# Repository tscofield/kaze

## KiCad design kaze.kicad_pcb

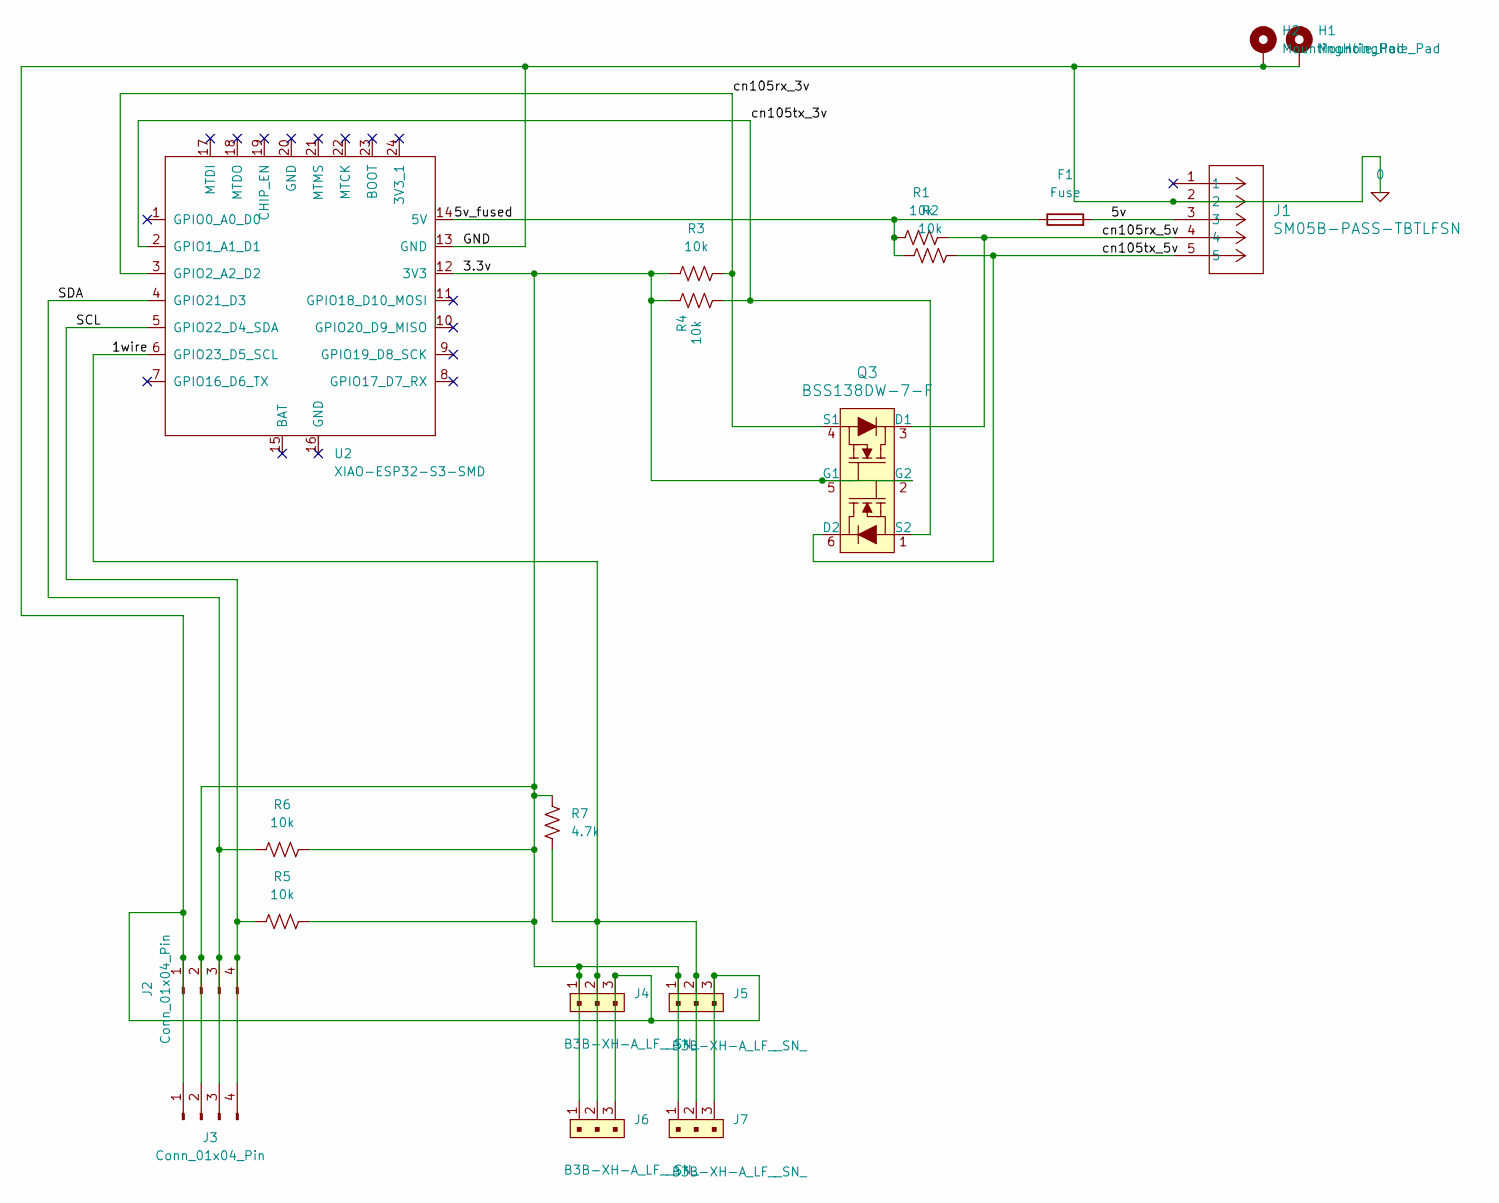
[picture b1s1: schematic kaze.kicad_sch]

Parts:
F1: Fuse; Fuse_0805_2012Metric
H1, H2: MountingHole_Pad; MountingHole_3.2mm_M3_Pad_TopBottom
J1: SM05B-PASS-TBTLFSN; CONN_S05B-PASK-2_JST
J2, J3: Conn_01x04_Pin; JST_XH_S4B-XH-A-1_1x04_P2.50mm_Horizontal
J4, J5, J6, J7: B3B-XH-A_LF__SN_; JST_XH_S3B-XH-A-1_1x03_P2.50mm_Horizontal; MPN B3B-XH-A(LF)(SN); Digi-Key_PN 455-2248-ND
Q3: BSS138DW-7-F; SOT-23-6; MPN BSS138DW-7-F; Digi-Key_PN BSS138DW-FDICT-ND
R1, R2, R3, R4, R5, R6: 10k; R_0805_2012Metric_Pad1.20x1.40mm_HandSolder
R7: 4.7k; R_0805_2012Metric_Pad1.20x1.40mm_HandSolder
U2: XIAO-ESP32-S3-SMD; XIAO-ESP32-C6-SMD

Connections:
0: H1.1 (1_1), H2.1 (1_1), J1.2, J2.1, J3.1, J4.3, J5.3, J6.3, J7.3, U2.13 (GND)
/1wire: J4.2, J5.2, J6.2, J7.2, R7.2, U2.6 (GPIO23_D5_SCL)
/3.3v: J2.2, J3.2, J4.1, J5.1, J6.1, J7.1, Q3.2 (G2), Q3.5 (G1), R3.2, R4.1, R5.1, R6.2, R7.1, U2.12 (3V3)
/5v: F1.2, J1.3
/5v_fused: F1.1, R1.1, R2.2, U2.14 (5V)
/SCL: J2.4, J3.4, R5.2, U2.5 (GPIO22_D4_SDA)
/SDA: J2.3, J3.3, R6.1, U2.4 (GPIO21_D3)
/cn105rx_3v: Q3.4 (S1), R3.1, U2.3 (GPIO2_A2_D2)
/cn105rx_5v: J1.4, Q3.3 (D1), R1.2
/cn105tx_3v: Q3.1 (S2), R4.2, U2.2 (GPIO1_A1_D1)
/cn105tx_5v: J1.5, Q3.6 (D2), R2.1

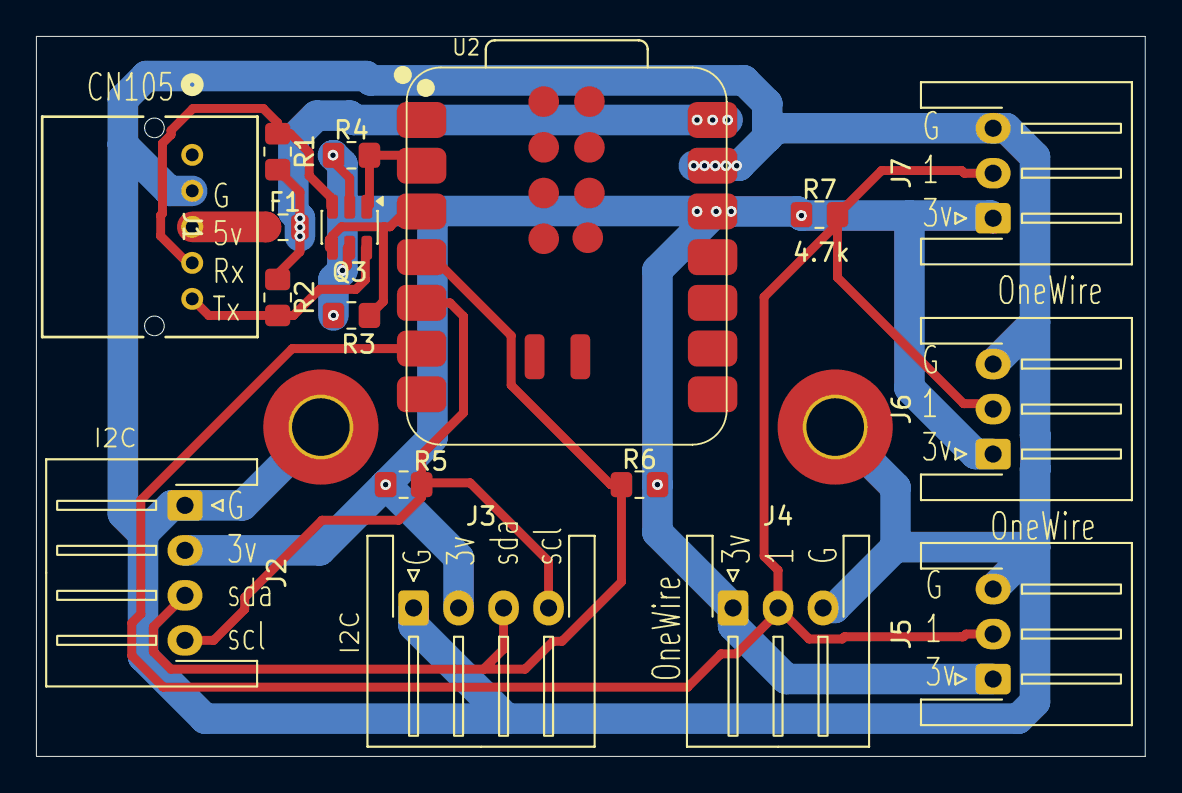
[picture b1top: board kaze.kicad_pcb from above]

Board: 2 copper layers, 61.6 x 40.0 mm, 20 parts (1 on the bottom side), 11 nets.

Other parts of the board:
kobee-studio-6AB488DE: Kobee Studio; kobee-studio-6AB48870
